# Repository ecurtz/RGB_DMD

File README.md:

# RGB_DMD LED Matrix Display for Pinball #

RGB_DMD is software for displaying either colorized signals from a pinball machine or color images from a host PC onto RGB LED matrix displays using the [Teensy 3.2](http://www.pjrc.com/teensy/index.html) development board and a custom carrier board. RGB_DMD was written by Eli Curtz, <eli@nuprometheus.com> but is built on top of open source work by many people, primarily the [SmartMatrix](http://docs.pixelmatix.com/SmartMatrix/library.html) display library.

## Contents ##
### License ###
The RGB_DMD source code is released under the MIT License.
### HEX Folder ###
Contains compiled .hex versions of the project, which can be loaded directly to the board using the Teensy Loader  or Teensy Qt applications.
### SRC Folder ###
Contains the Arduino / C++ source code for the project.
### UTIL Folder ###
Utilities for testing and configuring data.

## Building RGB_DMD ##

### Tools ###
[Arduino IDE](http://arduino.cc/en/main/software) is required for recompiling RGB_DMD from source or customizing the code.

[Teensyduino](http://www.pjrc.com/teensy/td_download.html) is a required plugin that adds Teensy support to the Arduino IDE as well as the Teensy Loader tool for transferring compiled code to the development board.

### Libraries
These are additional third party code required when building RGB_DMD. They are distributed as source on github and are installed as described under __Manual Installation__ at the [Arduino reference](https://www.arduino.cc/en/Guide/Libraries#toc5).

[SmartMatrix](https://github.com/ecurtz/SmartMatrix) is used for outputting the signal to the RGB matrix. Link is to my fork which is required for hardware compatibility and has some optimizations.

[FastCRC](https://github.com/FrankBoesing/FastCRC) is used to calculate a checksum for DMD frames so they can be uniquely identified.

### Settings ###
The Arduino IDE should be set to compile for Teensy by selecting __Teensy 3.1__ from the __Tools : Board__ menu in the Arduino IDE.

RGB_DMD should be built to run at the __96MHz optimized (overclock)__ setting using the __Tools : CPU Speed__ menu.

## Using DMD Input ##
Pinball machines use a set of 6 signals to control a plasma or LED DMD. RGB_DMD captures these inputs to determine which CPU system the pin is using and rebuild the display images.

__DOT CLOCK__: Repeatedly switches between high and low to mark when the dot data should be read.
__DOT DATA__: Will be either on or off for each of the 128 dots in a single row of the DMD.
__COLUMN LATCH__: Marks the end of the row of dot data.
__DISPLAY ENABLE__: Turns the actual display output on and off. By varying the display enable time the overall brightness can be adjusted, and varying the time for different data on the same row is used to produce the effect of multiple shades on a single color DMD.

__ROW CLOCK__: Moves to the next display row. Separate from the column latch because one row may be updated and latched several times with different data before the transition.__ROW DATA__: Used with row clock to mark the transition from the last row back to the first.

## Using USB Input ##
RGB_DMD may be controlled over USB from a host computer to store settings for the DMD input or display full color images for homebrew pinball machines.
### Sending From Python ###
Using USB input from Python requires the [PySerial Extension](https://pyserial.readthedocs.org/en/latest/). If you are using [PyProcGame](http://pyprocgame.pindev.org) or the [Mission Pinball Framework](https://missionpinball.com) PySerial may already be installed.
### Sending From C/C++/C# ###

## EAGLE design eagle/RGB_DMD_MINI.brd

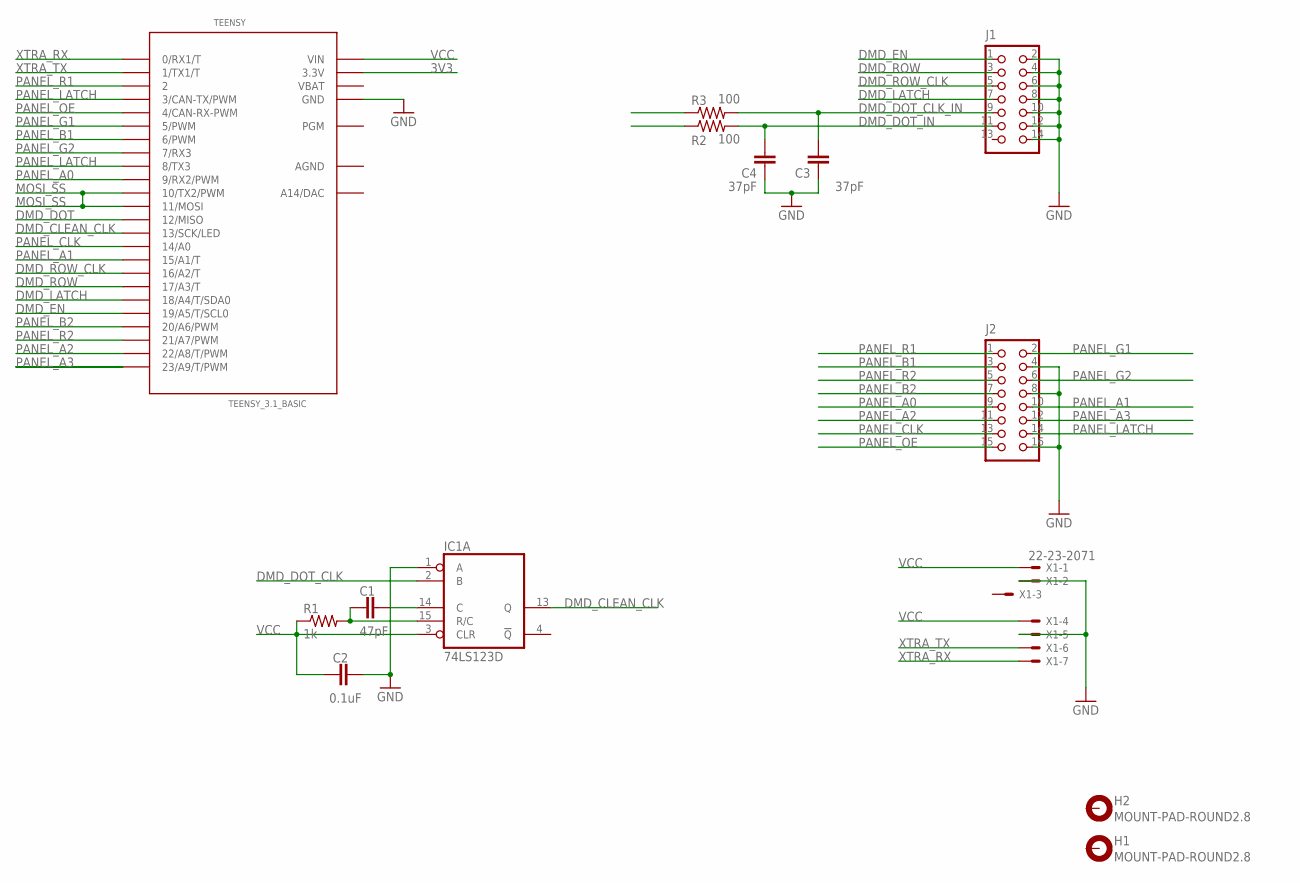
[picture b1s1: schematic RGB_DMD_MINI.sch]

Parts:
C1: 47pF; C0603
C2: 0.1uF; C0603
C3, C4: 37pF; C0603
H1, H2: MOUNT-PAD-ROUND2.8; 2,8-PAD
IC1: 74LS123D; SO16
J1: CON_HEADER_2X07-PTH-SHROUDED; PINSHRD_PTH_2X07
J2: CON_HEADER_2X08-PTH-SHROUDED; PINSHRD_PTH_2X08
R1: 1k; R0603
R2, R3: 100; R0603
TEENSY: TEENSY_3.1_BASIC
X1: 22-23-2071

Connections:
3V3: TEENSY.3.3V, TEENSY.3.3V1 (3.3V)
AGND: TEENSY.AGND
DMD_CLEAN_CLK: IC1.13 (Q), TEENSY.13 (13/SCK/LED)
DMD_DOT: R2.1, TEENSY.12 (12/MISO)
DMD_DOT_CLK: IC1.2 (B), R3.1
DMD_DOT_CLK_IN: C3.2, J1.9, R3.2
DMD_DOT_IN: C4.2, J1.11, R2.2
DMD_EN: J1.1, TEENSY.19/A5 (19/A5/T/SCL0)
DMD_LATCH: J1.7, TEENSY.18/A4 (18/A4/T/SDA0)
DMD_ROW: J1.3, TEENSY.17/A3 (17/A3/T)
DMD_ROW_CLK: J1.5, TEENSY.16/A2 (16/A2/T)
GND: C2.2, C3.1, C4.1, IC1.1 (A), IC1.8 (GND), J1.2, J1.4, J1.6, J1.8, J1.10, J1.12, J1.14, J2.4, J2.8, J2.16, TEENSY.GND, TEENSY.GND1 (GND), X1.2, X1.5
MOSI_SS: TEENSY.10 (10/TX2/PWM), TEENSY.11 (11/MOSI)
unnamed: C1.1, IC1.15 (R/C), R1.2
unnamed: C1.2, IC1.14 (C)
PANEL_A0: J2.9, TEENSY.9 (9/RX2/PWM)
PANEL_A1: J2.10, TEENSY.15/A1 (15/A1/T)
PANEL_A2: J2.11, TEENSY.22/A8 (22/A8/T/PWM)
PANEL_A3: J2.12, TEENSY.23/A9 (23/A9/T/PWM)
PANEL_B1: J2.3, TEENSY.6 (6/PWM)
PANEL_B2: J2.7, TEENSY.20/A6 (20/A6/PWM)
PANEL_CLK: J2.13, TEENSY.14/A0
PANEL_G1: J2.2, TEENSY.5 (5/PWM)
PANEL_G2: J2.6, TEENSY.7 (7/RX3)
PANEL_LATCH: J2.14, TEENSY.3 (3/CAN-TX/PWM), TEENSY.8 (8/TX3)
PANEL_OE: J2.15, TEENSY.4 (4/CAN-RX-PWM)
PANEL_R1: J2.1, TEENSY.2
PANEL_R2: J2.5, TEENSY.21/A7 (21/A7/PWM)
VBAT: TEENSY.VBAT
VCC: C2.1, IC1.3 (CLR), IC1.16 (VCC), R1.1, TEENSY.VIN, X1.1, X1.4
XTRA_RX: TEENSY.0 (0/RX1/T), X1.7
XTRA_TX: TEENSY.1 (1/TX1/T), X1.6

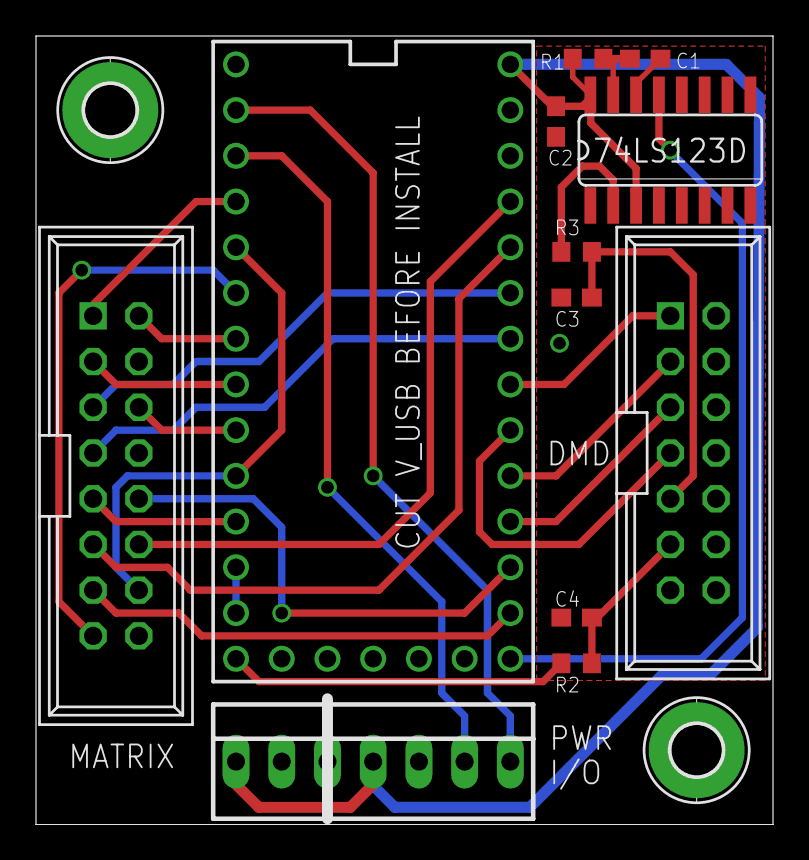
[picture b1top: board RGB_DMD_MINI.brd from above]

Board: 2 copper layers, 40.9 x 43.8 mm, 14 parts (0 on the bottom side), 30 nets.

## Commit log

2016-02-07 Added to README.md
2016-02-07 Additions to README.md
2016-02-09 Crazy SAM bug where it missed the marker to begin SPI because of the timing between the IRQ and the row clock. Disabled the IRQ until frame processing begins.
2016-02-09 Updated version number for SAM fix.
2016-02-13 Initial Gottlieb/Premier input code.
2016-02-18 Update to the test signal generators - Gottlieb/Premier added, and a bug in WPC fixed
2016-02-29 Initial code for alternate input relying on SPI transfer completion rather than end of row signals. Fixed (?) stray pixel getting set in field which appeared in certain combinations of build settings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
2016-05-25 Commented out WIP detection of Gottlieb/Premier machines since several users have had WPC machines misidentified and the code is very WIP.
2016-06-12 Updated simulated DMD output sketches and added Whitestar.
2016-06-12 Added weird extra row zero latch from early Whitestar games and reversed biplane order.
2017-01-31 Added Eagle files for the RGB DMD Mini Teensy 3.2 carrier board.
2017-06-15 Updated simulator code. Changed pins to support board I have extras of and added weird 33rd row to Gottlieb/Premier simulator.
2018-02-18 Simulation of Stern SPIKE platform DMD output added to util folder.
2020-08-31 Added an svg file of a basic DMD sized frame for attaching the panels. In the format used by Ponoko.com for laser cutting, so lines are very faint by default.
2023-11-14 Added collection of Saleae Logic recordings of DMD data
